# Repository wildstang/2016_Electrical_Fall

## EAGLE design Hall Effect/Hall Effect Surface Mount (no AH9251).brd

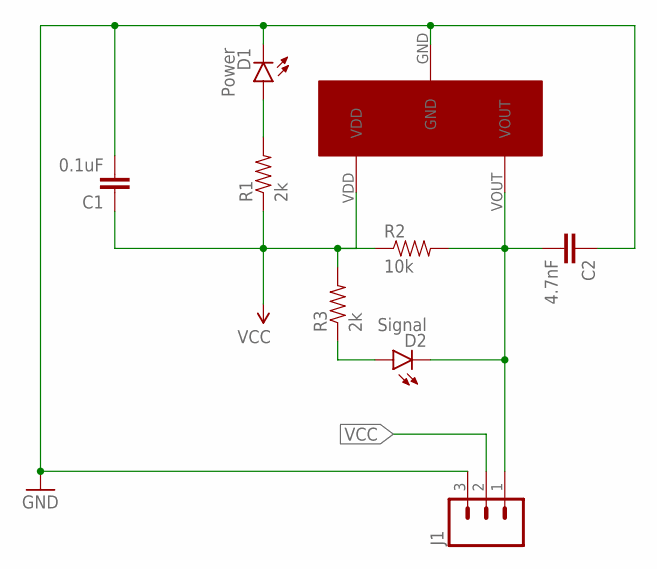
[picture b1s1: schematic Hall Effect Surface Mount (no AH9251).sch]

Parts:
C1: 0.1uF; 0603-CAP
C2: 4.7nF; 0603-CAP
D1: Power; LED-0603
D2: Signal; LED-0603
J1: M03PTH; 1X03
R1, R3: 2k; 0603-RES
R2: 10k; 0603-RES
U$1: US5881-HALL-EFFECT

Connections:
GND: C1.2, C2.1, D1.C, J1.3, U$1.GND
unnamed: D1.A, R1.2
unnamed: D2.A, R3.1
unnamed: C2.2, D2.C, J1.1, R2.2, U$1.VOUT
VCC: C1.1, J1.2, R1.1, R2.1, R3.2, U$1.VDD

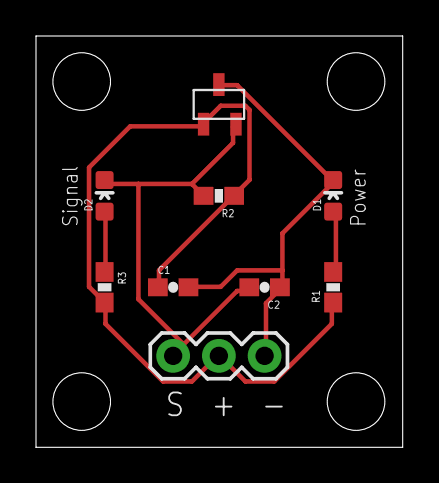
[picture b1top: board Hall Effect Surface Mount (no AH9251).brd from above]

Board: 2 copper layers, 20.4 x 22.9 mm, 9 parts (0 on the bottom side), 5 nets.

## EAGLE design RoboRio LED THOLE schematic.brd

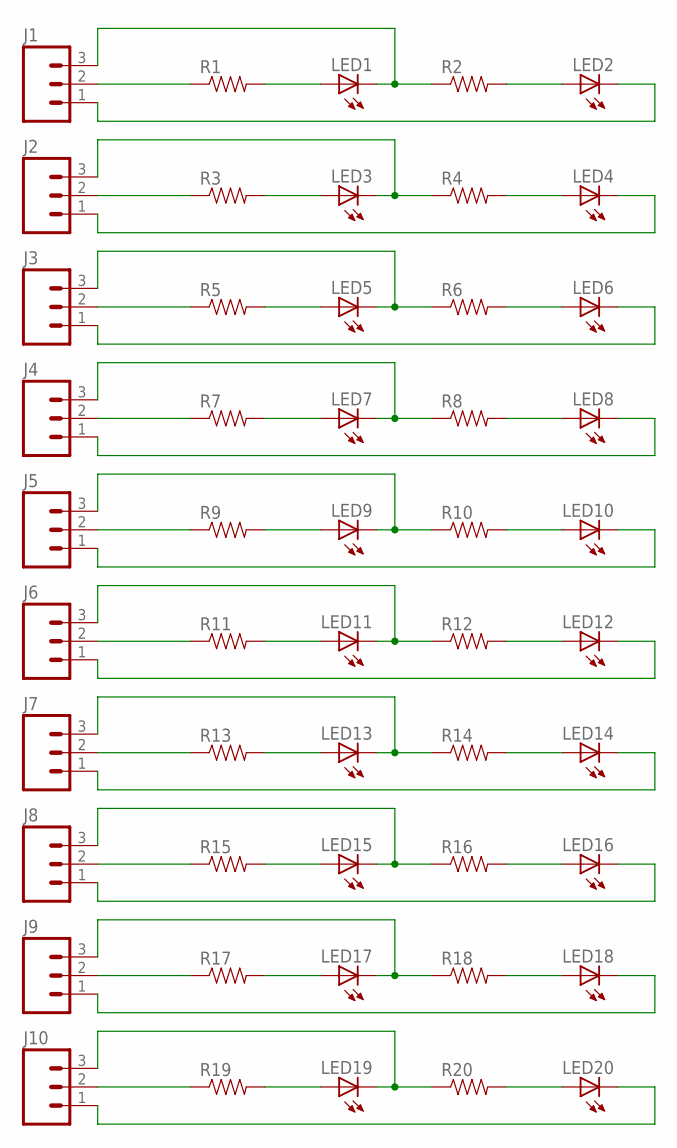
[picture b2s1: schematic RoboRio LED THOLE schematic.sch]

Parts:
J1, J2, J3, J4, J5, J6, J7, J8, J9, J10: M03PTH; 1X03
LED1, LED2, LED3, LED4, LED5, LED6, LED7, LED8, LED9, LED10, LED11, LED12, LED13, LED14, LED15, LED16, LED17, LED18, LED19, LED20: LED3MM
R1, R2, R3, R4, R5, R6, R7, R8, R9, R10, R11, R12, R13, R14, R15, R16, R17, R18, R19, R20: RESISTORKIT; AXIAL-0.3-KIT

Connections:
GND: J1.1, LED2.K (C)
GND1: J2.1, LED4.K (C)
GND2: J3.1, LED6.K (C)
GND3: J4.1, LED8.K (C)
GND4: J5.1, LED10.K (C)
GND5: J6.1, LED12.K (C)
GND6: J7.1, LED14.K (C)
GND7: J8.1, LED16.K (C)
GND8: J9.1, LED18.K (C)
GND9: J10.1, LED20.K (C)
unnamed: J1.2, R1.P$1 (1)
unnamed: LED1.A, R1.P$2 (2)
unnamed: J2.2, R3.P$1 (1)
unnamed: LED2.A, R2.P$2 (2)
unnamed: LED4.A, R4.P$2 (2)
unnamed: LED3.A, R3.P$2 (2)
unnamed: J3.2, R5.P$1 (1)
unnamed: LED6.A, R6.P$2 (2)
unnamed: LED5.A, R5.P$2 (2)
unnamed: J4.2, R7.P$1 (1)
unnamed: LED8.A, R8.P$2 (2)
unnamed: LED7.A, R7.P$2 (2)
unnamed: J5.2, R9.P$1 (1)
unnamed: LED10.A, R10.P$2 (2)
unnamed: LED9.A, R9.P$2 (2)
unnamed: J6.2, R11.P$1 (1)
unnamed: LED12.A, R12.P$2 (2)
unnamed: LED11.A, R11.P$2 (2)
unnamed: J7.2, R13.P$1 (1)
unnamed: LED14.A, R14.P$2 (2)
unnamed: LED13.A, R13.P$2 (2)
unnamed: J8.2, R15.P$1 (1)
unnamed: LED16.A, R16.P$2 (2)
unnamed: LED15.A, R15.P$2 (2)
unnamed: J9.2, R17.P$1 (1)
unnamed: LED18.A, R18.P$2 (2)
unnamed: LED17.A, R17.P$2 (2)
unnamed: J10.2, R19.P$1 (1)
unnamed: LED20.A, R20.P$2 (2)
unnamed: LED19.A, R19.P$2 (2)
S: J1.3, LED1.K (C), R2.P$1 (1)
S1: J2.3, LED3.K (C), R4.P$1 (1)
S2: J3.3, LED5.K (C), R6.P$1 (1)
S3: J4.3, LED7.K (C), R8.P$1 (1)
S4: J5.3, LED9.K (C), R10.P$1 (1)
S5: J6.3, LED11.K (C), R12.P$1 (1)
S6: J7.3, LED13.K (C), R14.P$1 (1)
S7: J8.3, LED15.K (C), R16.P$1 (1)
S8: J9.3, LED17.K (C), R18.P$1 (1)
S9: J10.3, LED19.K (C), R20.P$1 (1)

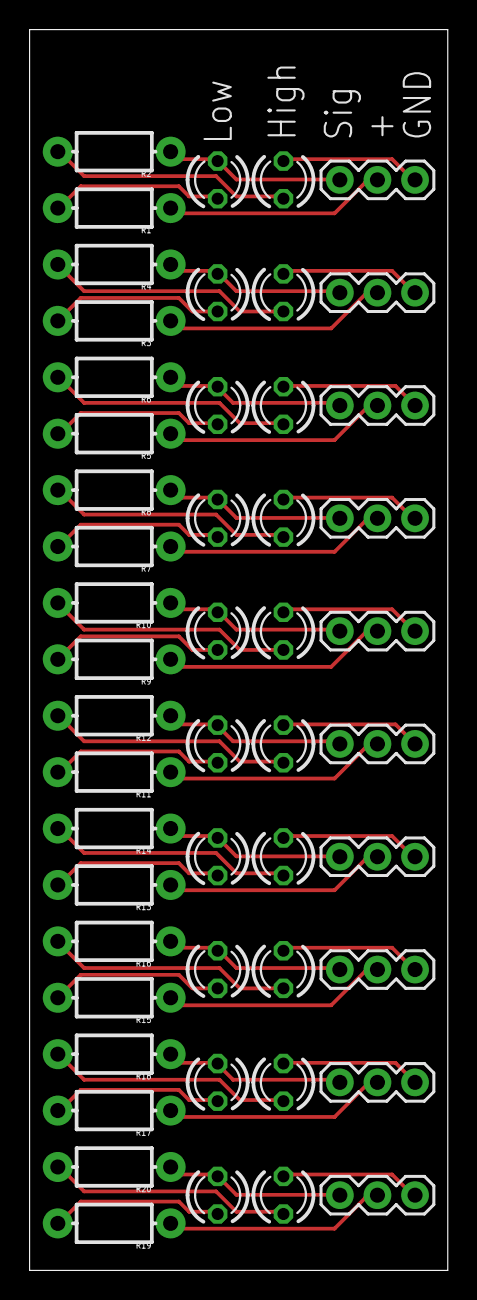
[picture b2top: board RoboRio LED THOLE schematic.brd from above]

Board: 2 copper layers, 28.2 x 83.8 mm, 50 parts (0 on the bottom side), 50 nets.

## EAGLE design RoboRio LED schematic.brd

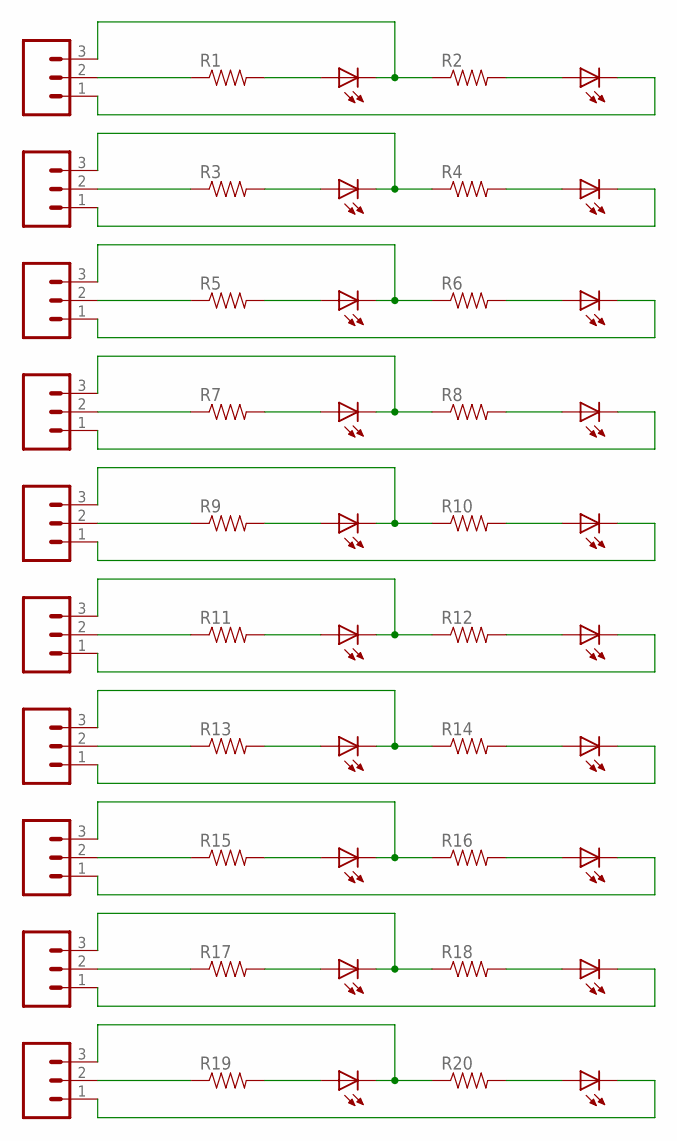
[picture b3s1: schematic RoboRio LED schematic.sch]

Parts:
D1, D2, D3, D4, D5, D6, D7, D8, D9, D10, D11, D12, D13, D14, D15, D16, D17, D18, D19, D20: LED1206; LED-1206
J1, J2, J3, J4, J5, J6, J7, J8, J9, J10: M03PTH; 1X03
R1, R2, R3, R4, R5, R6, R7, R8, R9, R10, R11, R12, R13, R14, R15, R16, R17, R18, R19, R20: RESISTOR0603-RES; 0603-RES

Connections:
GND: D2.C, J1.1
GND1: D4.C, J2.1
GND2: D6.C, J3.1
GND3: D8.C, J4.1
GND4: D10.C, J5.1
GND5: D12.C, J6.1
GND6: D14.C, J7.1
GND7: D16.C, J8.1
GND8: D18.C, J9.1
GND9: D20.C, J10.1
unnamed: J1.2, R1.1
unnamed: D1.A, R1.2
unnamed: J2.2, R3.1
unnamed: D2.A, R2.2
unnamed: D4.A, R4.2
unnamed: D3.A, R3.2
unnamed: J3.2, R5.1
unnamed: D6.A, R6.2
unnamed: D5.A, R5.2
unnamed: J4.2, R7.1
unnamed: D8.A, R8.2
unnamed: D7.A, R7.2
unnamed: J5.2, R9.1
unnamed: D10.A, R10.2
unnamed: D9.A, R9.2
unnamed: J6.2, R11.1
unnamed: D12.A, R12.2
unnamed: D11.A, R11.2
unnamed: J7.2, R13.1
unnamed: D14.A, R14.2
unnamed: D13.A, R13.2
unnamed: J8.2, R15.1
unnamed: D16.A, R16.2
unnamed: D15.A, R15.2
unnamed: J9.2, R17.1
unnamed: D18.A, R18.2
unnamed: D17.A, R17.2
unnamed: J10.2, R19.1
unnamed: D20.A, R20.2
unnamed: D19.A, R19.2
S: D1.C, J1.3, R2.1
S1: D3.C, J2.3, R4.1
S2: D5.C, J3.3, R6.1
S3: D7.C, J4.3, R8.1
S4: D9.C, J5.3, R10.1
S5: D11.C, J6.3, R12.1
S6: D13.C, J7.3, R14.1
S7: D15.C, J8.3, R16.1
S8: D17.C, J9.3, R18.1
S9: D19.C, J10.3, R20.1

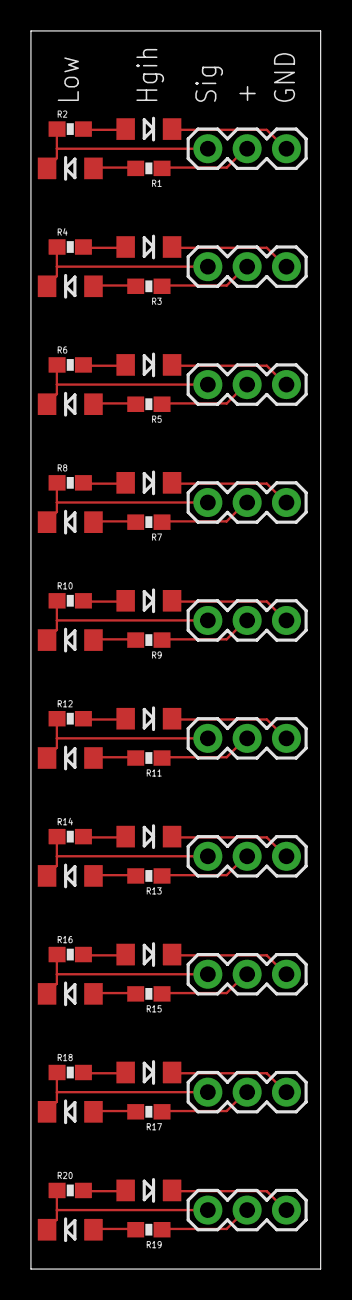
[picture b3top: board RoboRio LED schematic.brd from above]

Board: 2 copper layers, 18.7 x 80.0 mm, 50 parts (0 on the bottom side), 50 nets.

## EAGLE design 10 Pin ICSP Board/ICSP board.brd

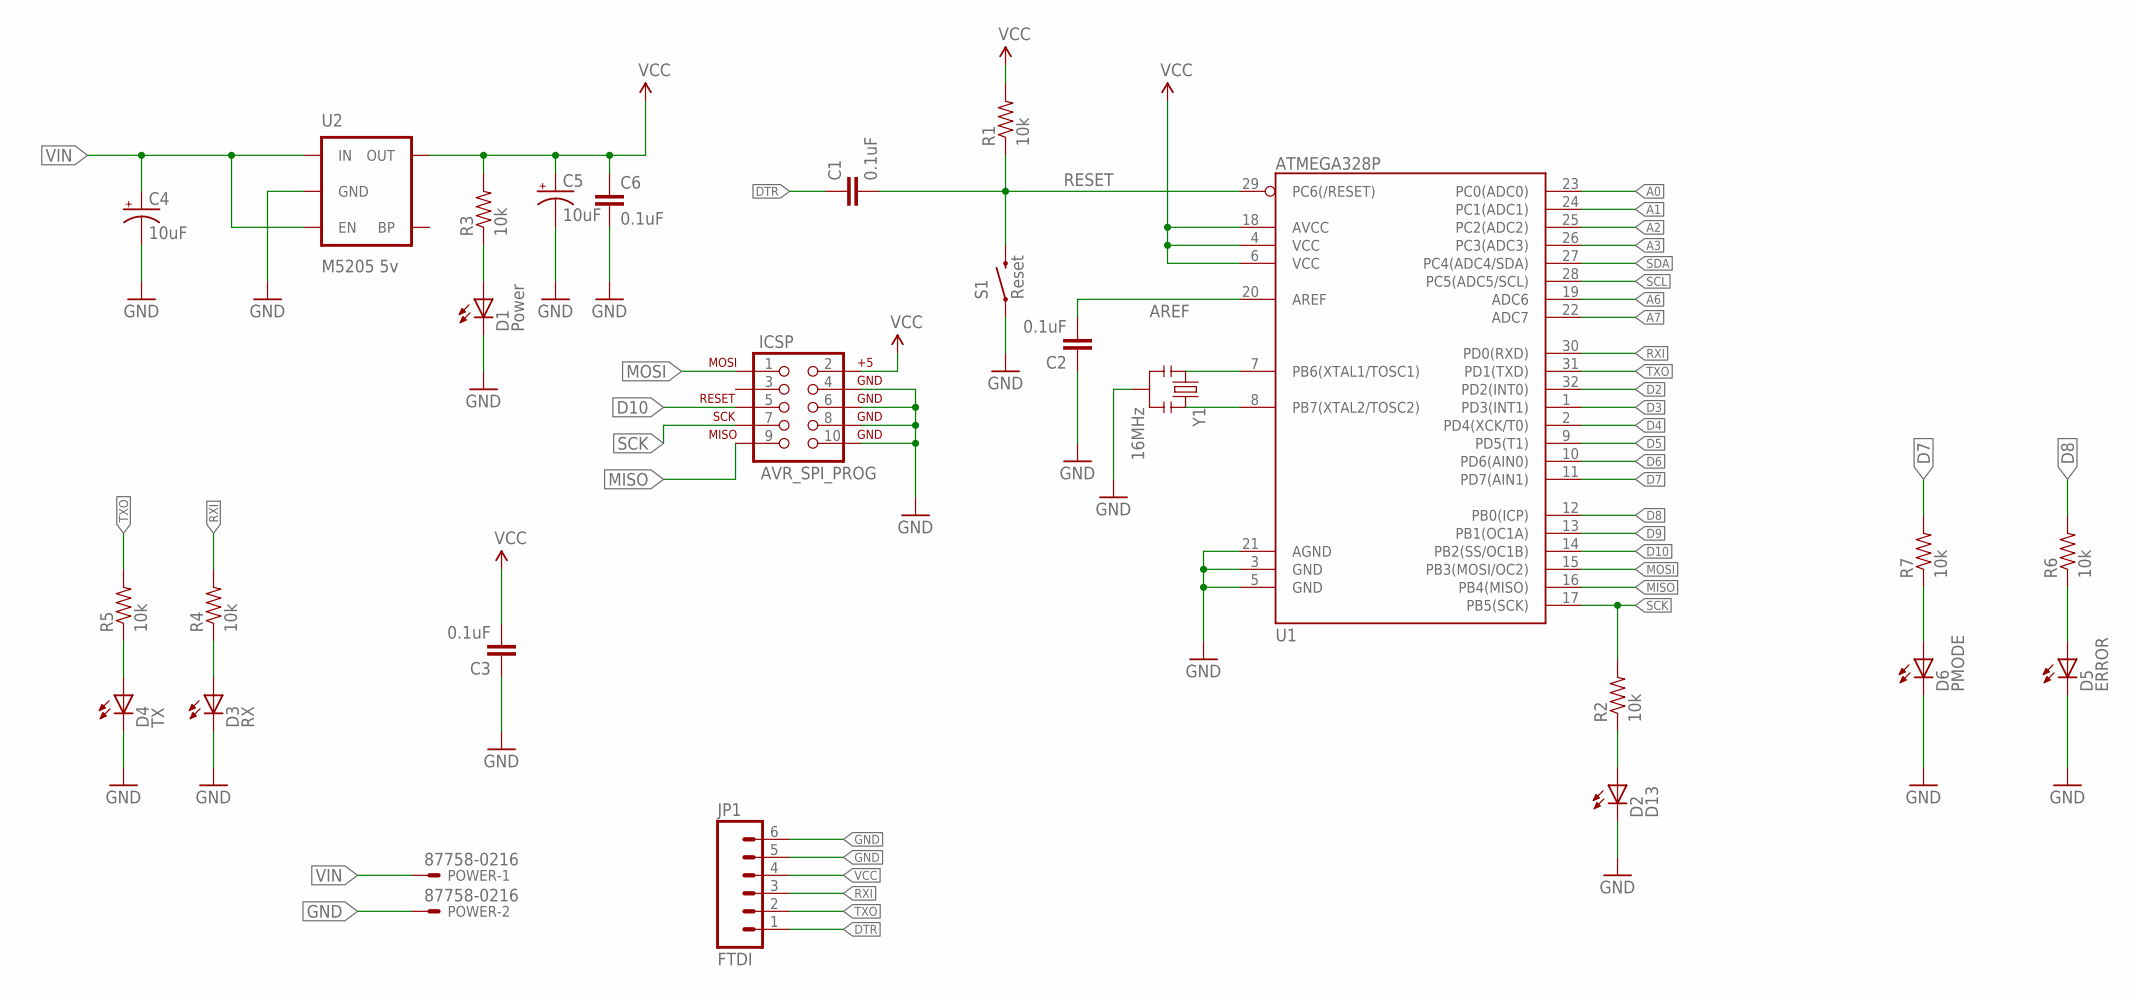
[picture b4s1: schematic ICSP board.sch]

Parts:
C1, C2, C3, C6: 0.1uF; 0603-CAP
C4, C5: 10uF; EIA3216
D1: Power; LED-0603
D2: D13; LED-0603
D3: RX; LED-0603
D4: TX; LED-0603
D5: ERROR; LED-0603
D6: PMODE; LED-0603
ICSP: AVR_SPI_PROG; AVR_ICSP
JP1: FTDI; 1X06
POWER: 87758-0216
R1, R2, R3, R4, R5, R6, R7: 10k; 0603-RES
S1: Reset; TACTILE_SWITCH_SMD
U1: ATMEGA328P; TQFP32-08
U2: M5205 5v; SOT23-5
Y1: 16MHz; RESONATOR-SMD

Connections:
A0: U1.23 (PC0(ADC0))
A1: U1.24 (PC1(ADC1))
A2: U1.25 (PC2(ADC2))
A3: U1.26 (PC3(ADC3))
A6: U1.19 (ADC6)
A7: U1.22 (ADC7)
AREF: C2.2, U1.20 (AREF)
D2: U1.32 (PD2(INT0))
D3: U1.1 (PD3(INT1))
D4: U1.2 (PD4(XCK/T0))
D5: U1.9 (PD5(T1))
D6: U1.10 (PD6(AIN0))
D7: R7.2, U1.11 (PD7(AIN1))
D8: R6.2, U1.12 (PB0(ICP))
D9: U1.13 (PB1(OC1A))
D10: ICSP.5, U1.14 (PB2(SS/OC1B))
DTR: C1.1, JP1.1
GND: C2.1, C3.1, C4.C (-), C5.C (-), C6.2, D1.C, D2.C, D3.C, D4.C, D5.C, D6.C, ICSP.4, ICSP.6, ICSP.8, ICSP.10, JP1.5, JP1.6, POWER.2, S1.1, U1.3 (GND), U1.5 (GND), U1.21 (AGND), U2.2 (GND), Y1.2
MISO: ICSP.9, U1.16 (PB4(MISO))
MOSI: ICSP.1, U1.15 (PB3(MOSI/OC2))
unnamed: U1.7 (PB6(XTAL1/TOSC1)), Y1.1
unnamed: U1.8 (PB7(XTAL2/TOSC2)), Y1.3
unnamed: D1.A, R3.1
unnamed: D2.A, R2.1
unnamed: D3.A, R4.1
unnamed: D4.A, R5.1
unnamed: D5.A, R6.1
unnamed: D6.A, R7.1
RESET: C1.2, R1.1, S1.3 (2), U1.29 (PC6(/RESET))
RXI: JP1.3, R4.2, U1.30 (PD0(RXD))
SCK: ICSP.7, R2.2, U1.17 (PB5(SCK))
SCL: U1.28 (PC5(ADC5/SCL))
SDA: U1.27 (PC4(ADC4/SDA))
TXO: JP1.2, R5.2, U1.31 (PD1(TXD))
VCC: C3.2, C5.A (+), C6.1, ICSP.2, JP1.4, R1.2, R3.2, U1.4 (VCC), U1.6 (VCC), U1.18 (AVCC), U2.5 (OUT)
VIN: C4.A (+), POWER.1, U2.1 (IN), U2.3 (EN)

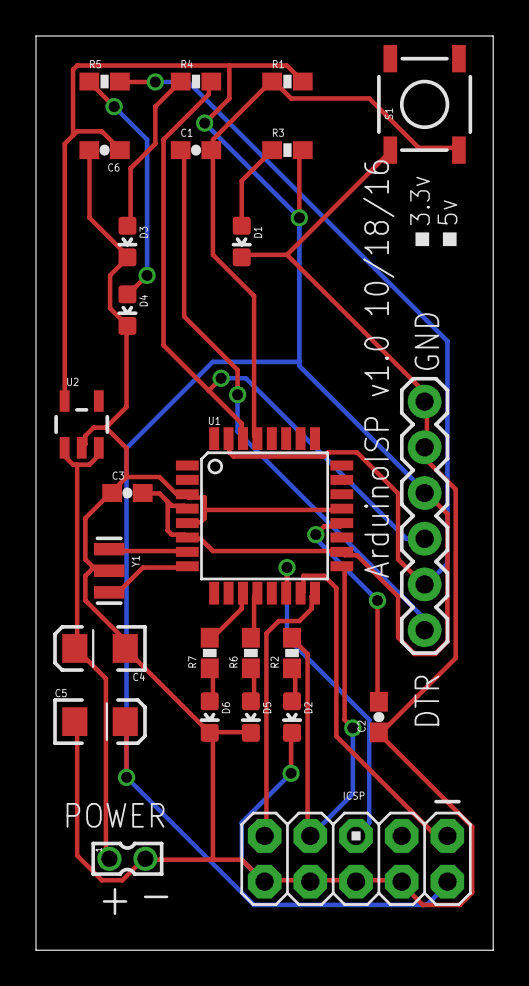
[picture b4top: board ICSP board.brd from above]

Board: 2 copper layers, 25.4 x 50.8 mm, 26 parts (0 on the bottom side), 22 nets.

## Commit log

2016-09-13 New repo
2016-09-13 Initial commit for adruino clone
2016-09-21 Added base Arduino clone schemtic
2016-09-30 Advanced Electrical Project - Jordan - Schematic - RoboRio LED Board
2016-09-30 Jordan - RoboRio LED fixed
2016-09-30 Jordan RoboRio LED Final
2016-10-04 Advanced Electrical project - Jordan Kiel - finished board
2016-10-05 Advanced Electrical Project - Jordan Kiel - Surface Mount RoboRio LED
2016-10-05 Changed placement for one sub-circuit
2016-10-05 Trial layouts, smaller components, no need to review
2016-10-13 Added optical sensor schematic and board files for review
2016-10-17 updated boards
2016-10-17 Added 10 Pin to board. Still needs new power source.
2016-10-18 Added hall effect board from Patrick - added to other repo.
2016-10-18 Moved SMD RIO LED board into folder
2016-10-18 Updates to final board Changed power connector as discussed. Rotated some components for slightly better trace routing. Added labels to connectors and board date/version. Ready for fab.
2016-10-18 Completed schematic with correct part for sensor. Added component values
2016-10-19 Updated Optical encoder board with latest changes. Added 2 status LEDs to ICSP board.
2016-10-20 Add files via upload
    Matt and Jordan RoboRio LED project
2016-10-20 JIT board
2016-10-20 Added labels and removed component names from board.
2016-10-20 Routed the through hold board. Change LED component to indicate true component size
2016-10-20 Initial board design
2016-10-24 Create Parts_List

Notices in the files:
parts and their libraries:
SparkFun-Passives: Licensing: Creative Commons ShareAlike 4.0 International - https://creativecommons.org/licenses/by-sa/4.0
